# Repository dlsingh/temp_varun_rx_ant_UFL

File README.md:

this repo contains files rof varun rx with UFL antenna project

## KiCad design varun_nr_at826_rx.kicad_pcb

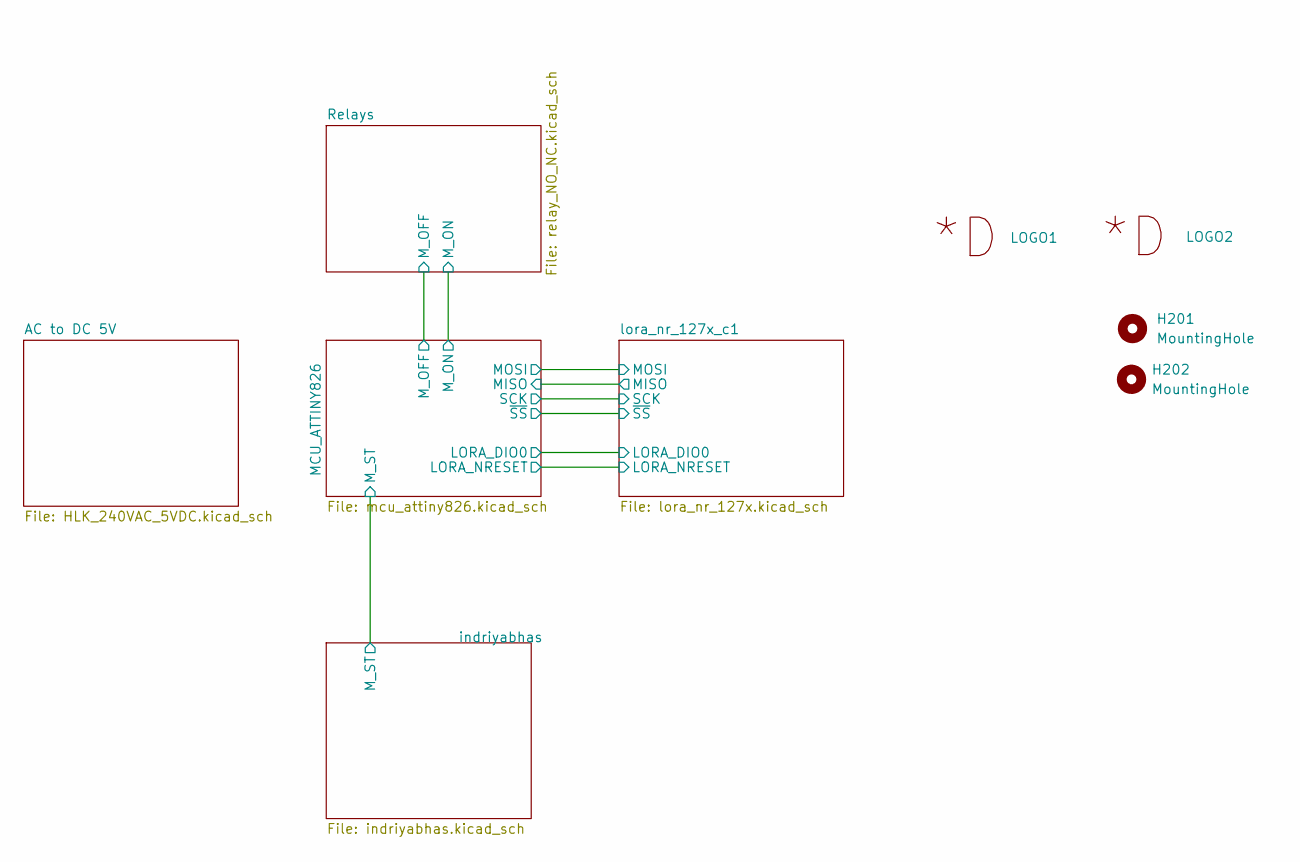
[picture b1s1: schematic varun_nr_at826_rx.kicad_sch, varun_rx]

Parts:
H201, H202: MountingHole; MountingHole_3mm
LOGO1, LOGO2: Dyulabs_logo; D_logo

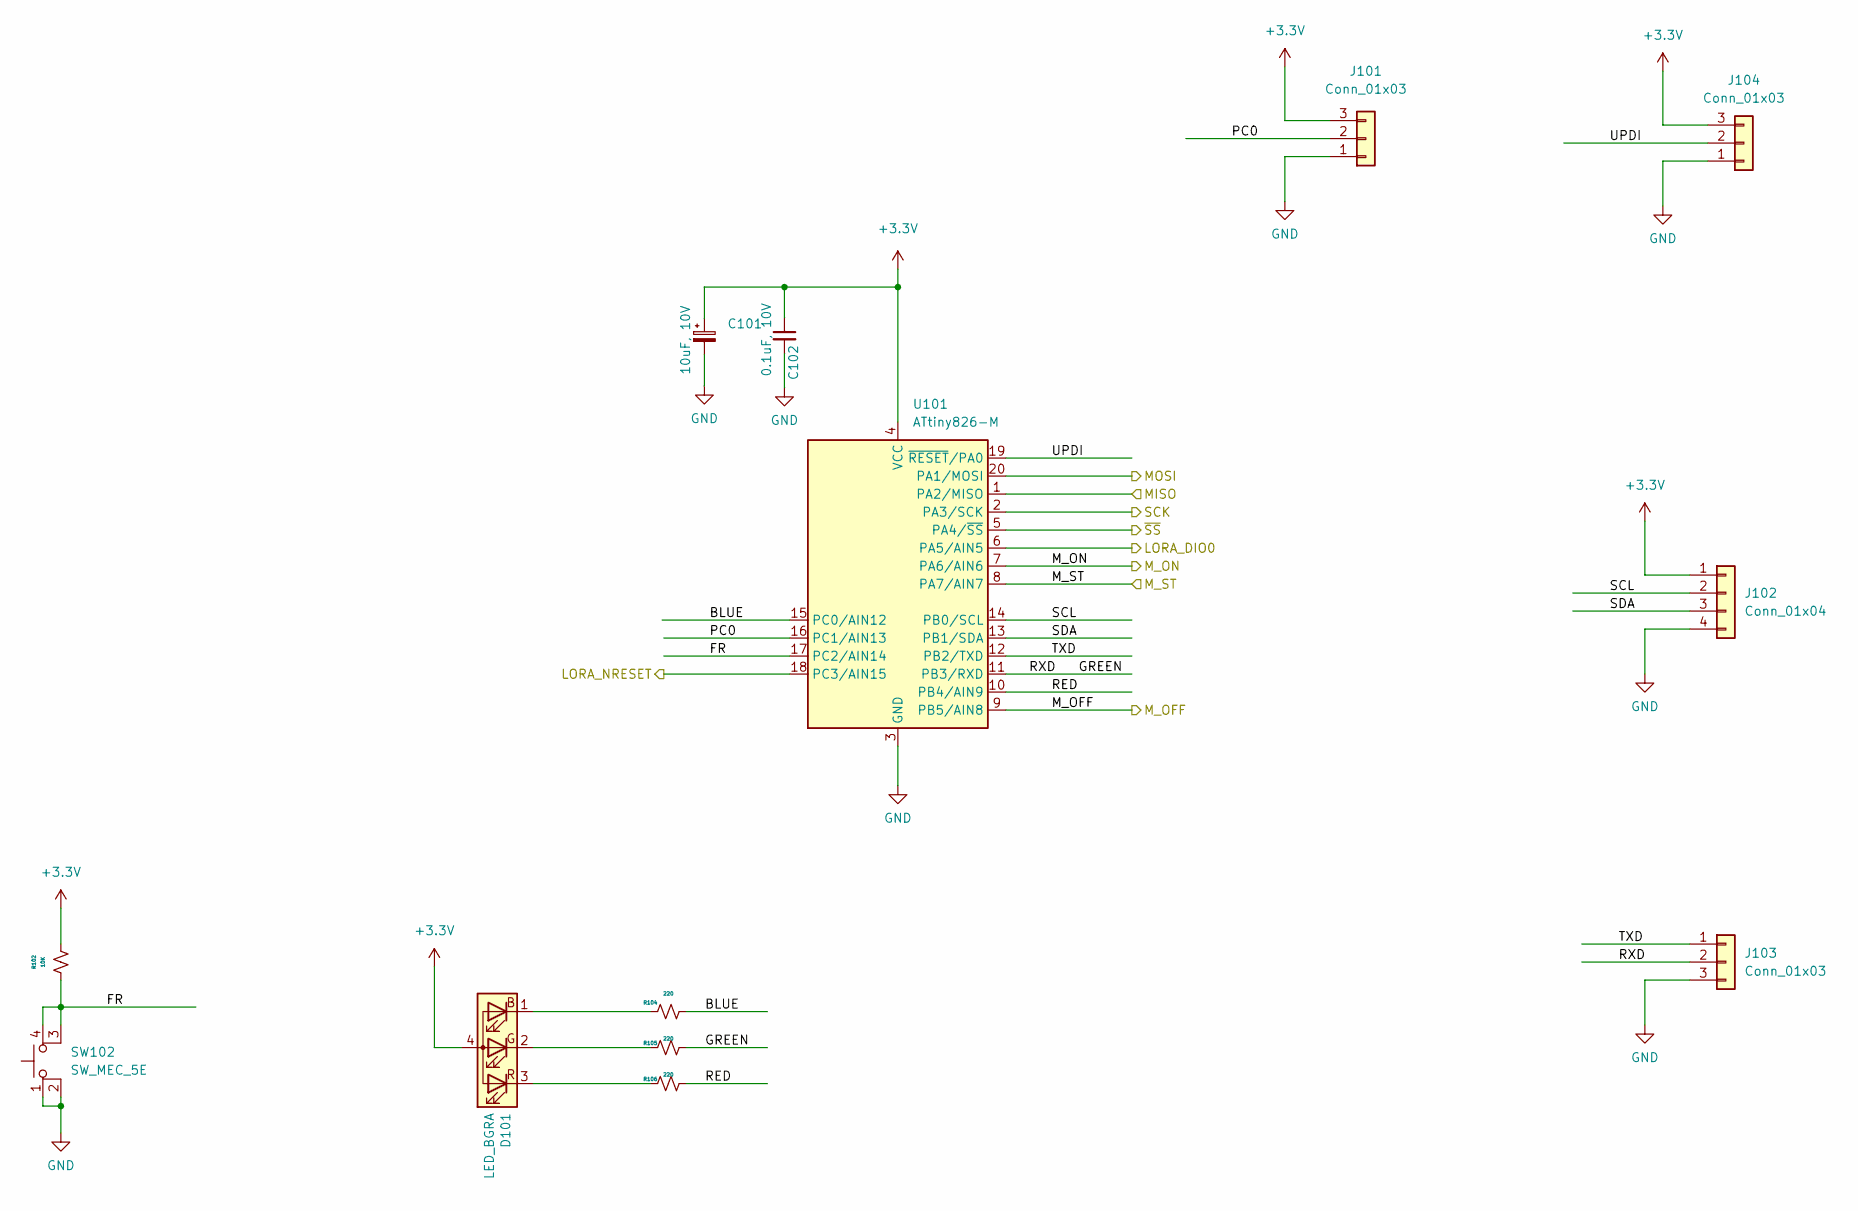
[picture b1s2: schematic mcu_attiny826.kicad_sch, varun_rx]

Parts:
C101: 10uF, 10V; C_1206_3216Metric
C102: 0.1uF, 10V; C_0402_1005Metric
D101: LED_BGRA; LED_Cree_RGB_1.00x1.00mm_P0.2mm
J101, J103: Conn_01x03; PinHeader_1x03_P2.54mm_Vertical
J102: Conn_01x04; PinHeader_1x04_P2.54mm_Vertical
J104: Conn_01x03; JST_PH_B3B-PH-K_1x03_P2.00mm_Vertical
R102: 10K; R_0402_1005Metric
R104, R105, R106: 220; R_0402_1005Metric
SW102: SW_MEC_5E; RKB2SJM250SMTR_LFS_SWITCH
U101: ATtiny826-M; VQFN-20-1EP_3x3mm_P0.4mm_EP1.7x1.7mm

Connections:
+3V3: C101.1, C102.1, D101.4 (A), J101.3, J102.1, J104.3, R102.2, U101.4 (VCC); also elsewhere on the board
/MCU_ATTINY826/BLUE: R104.1, U101.15 (PC0/AIN12)
/MCU_ATTINY826/FR: R102.1, SW102.3 (K), SW102.4 (A), U101.17 (PC2/AIN14)
/MCU_ATTINY826/GREEN: J103.2, R105.1, U101.11 (PB3/RXD)
/MCU_ATTINY826/LORA_DIO0: U101.6 (PA5/AIN5); also elsewhere on the board
/MCU_ATTINY826/LORA_NRESET: U101.18 (PC3/AIN15); also elsewhere on the board
/MCU_ATTINY826/MISO: U101.1 (PA2/MISO); also elsewhere on the board
/MCU_ATTINY826/MOSI: U101.20 (PA1/MOSI); also elsewhere on the board
/MCU_ATTINY826/M_OFF: U101.9 (PB5/AIN8); also elsewhere on the board
/MCU_ATTINY826/M_ON: U101.7 (PA6/AIN6); also elsewhere on the board
/MCU_ATTINY826/M_ST: U101.8 (PA7/AIN7); also elsewhere on the board
/MCU_ATTINY826/PC0: J101.2, U101.16 (PC1/AIN13)
/MCU_ATTINY826/RED: R106.1, U101.10 (PB4/AIN9)
/MCU_ATTINY826/SCK: U101.2 (PA3/SCK); also elsewhere on the board
/MCU_ATTINY826/SCL: J102.2, U101.14 (PB0/SCL)
/MCU_ATTINY826/SDA: J102.3, U101.13 (PB1/SDA)
/MCU_ATTINY826/TXD: J103.1, U101.12 (PB2/TXD)
/MCU_ATTINY826/UPDI: J104.2, U101.19 (~RESET/PA0)
/MCU_ATTINY826/~SS: U101.5 (PA4/~SS); also elsewhere on the board
GND: C101.2, C102.2, J101.1, J102.4, J103.3, J104.1, SW102.1, SW102.2, U101.3 (GND), U101.21 (GND); also elsewhere on the board
unnamed: D101.1 (BK), R104.2
unnamed: D101.2 (GK), R105.2
unnamed: D101.3 (RK), R106.2

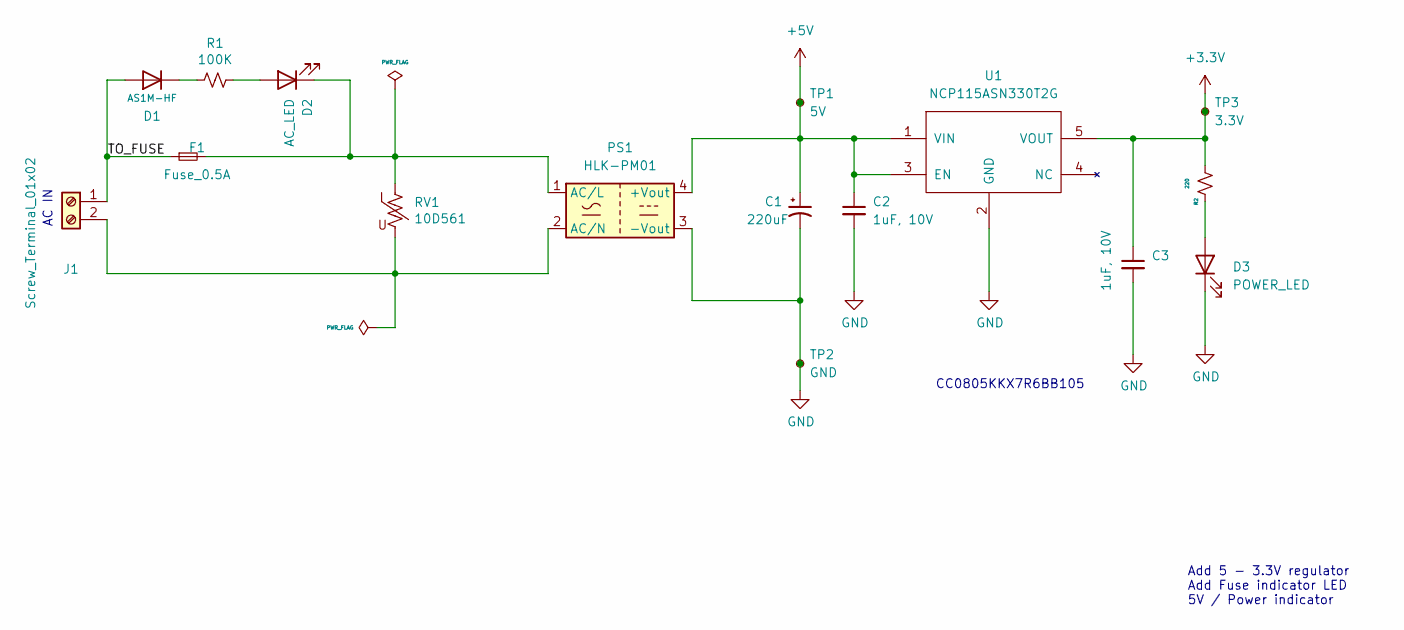
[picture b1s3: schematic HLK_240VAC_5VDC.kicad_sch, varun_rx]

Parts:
C1: 220uF; CP_Radial_D6.3mm_P2.50mm
C2, C3: 1uF, 10V; C_0805_2012Metric
D1: AS1M-HF; D_SMA
D2: AC_LED; LED_D3.0mm
D3: POWER_LED; LED_D3.0mm
F1: Fuse_0.5A; Fuse_Schurter_UMT250
J1: Screw_Terminal_01x02; CUI_TB002-500-02BE
PS1: HLK-PM01; Converter_ACDC_HiLink_HLK-PMxx
R1: 100K; R_0805_2012Metric
R2: 220; R_0402_1005Metric
RV1: 10D561; RV_Disc_D12mm_W5.1mm_P7.5mm
TP1: 5V; TestPoint_THTPad_D1.0mm_Drill0.5mm
TP2: GND; TestPoint_THTPad_D1.0mm_Drill0.5mm
TP3: 3.3V; TestPoint_THTPad_D1.0mm_Drill0.5mm
U1: NCP115ASN330T2G; TSOP-5_1.65x3.05mm_P0.95mm

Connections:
+3V3: C3.1, R2.1, TP3.1, U1.5 (VOUT); also elsewhere on the board
+5V: C1.1, C2.1, PS1.4 (+Vout), TP1.1, U1.1 (VIN), U1.3 (EN); also elsewhere on the board
/AC to DC 5V/TO_FUSE: D1.2 (A), F1.1, J1.1
GND: C1.2, C2.2, C3.2, D3.1 (K), PS1.3 (-Vout), TP2.1, U1.2 (GND); also elsewhere on the board
unnamed: D1.1 (K), R1.2
unnamed: D2.1 (K), F1.2, PS1.1 (AC/L), RV1.1
unnamed: D2.2 (A), R1.1
unnamed: D3.2 (A), R2.2
unnamed: J1.2, PS1.2 (AC/N), RV1.2

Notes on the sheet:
AC IN
CC0805KKX7R6BB105
Add 5 - 3.3V regulator Add Fuse indicator LED 5V / Power indicator

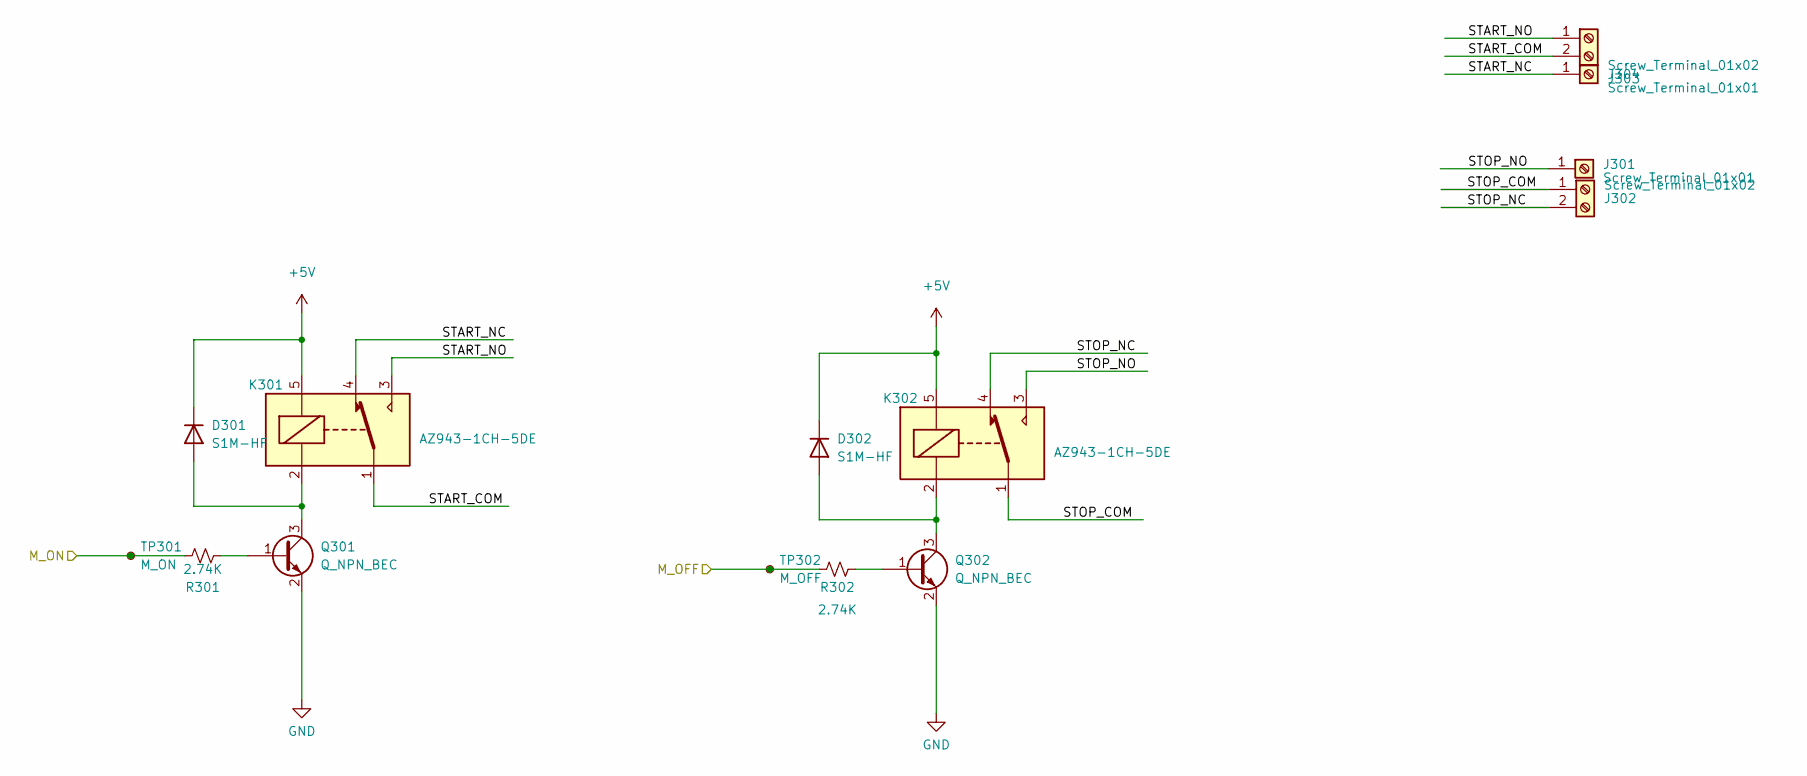
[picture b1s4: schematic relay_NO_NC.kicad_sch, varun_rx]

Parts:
D301, D302: S1M-HF; D_SMA
J301, J304: Screw_Terminal_01x01; PinHeader_1x01_P2.54mm_Vertical
J302, J303: Screw_Terminal_01x02; CUI_TB002-500-02BE
K301, K302: AZ943-1CH-5DE; Relay_SPDT_SANYOU_SRD_Series_Form_C
Q301, Q302: Q_NPN_BEC; TSOT-23
R301, R302: 2.74K; R_0402_1005Metric
TP301: M_ON; TestPoint_THTPad_D1.0mm_Drill0.5mm
TP302: M_OFF; TestPoint_THTPad_D1.0mm_Drill0.5mm

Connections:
+5V: D301.1 (K), D302.1 (K), K301.5, K302.5; also elsewhere on the board
/MCU_ATTINY826/M_OFF: R302.2, TP302.1; also elsewhere on the board
/MCU_ATTINY826/M_ON: R301.2, TP301.1; also elsewhere on the board
/Relays/START_COM: J303.2, K301.1
/Relays/START_NC: J304.1, K301.4
/Relays/START_NO: J303.1, K301.3
/Relays/STOP_COM: J302.1, K302.1
/Relays/STOP_NC: J302.2, K302.4
/Relays/STOP_NO: J301.1, K302.3
GND: Q301.2 (E), Q302.2 (E); also elsewhere on the board
unnamed: D301.2 (A), K301.2, Q301.3 (C)
unnamed: D302.2 (A), K302.2, Q302.3 (C)
unnamed: Q301.1 (B), R301.1
unnamed: Q302.1 (B), R302.1

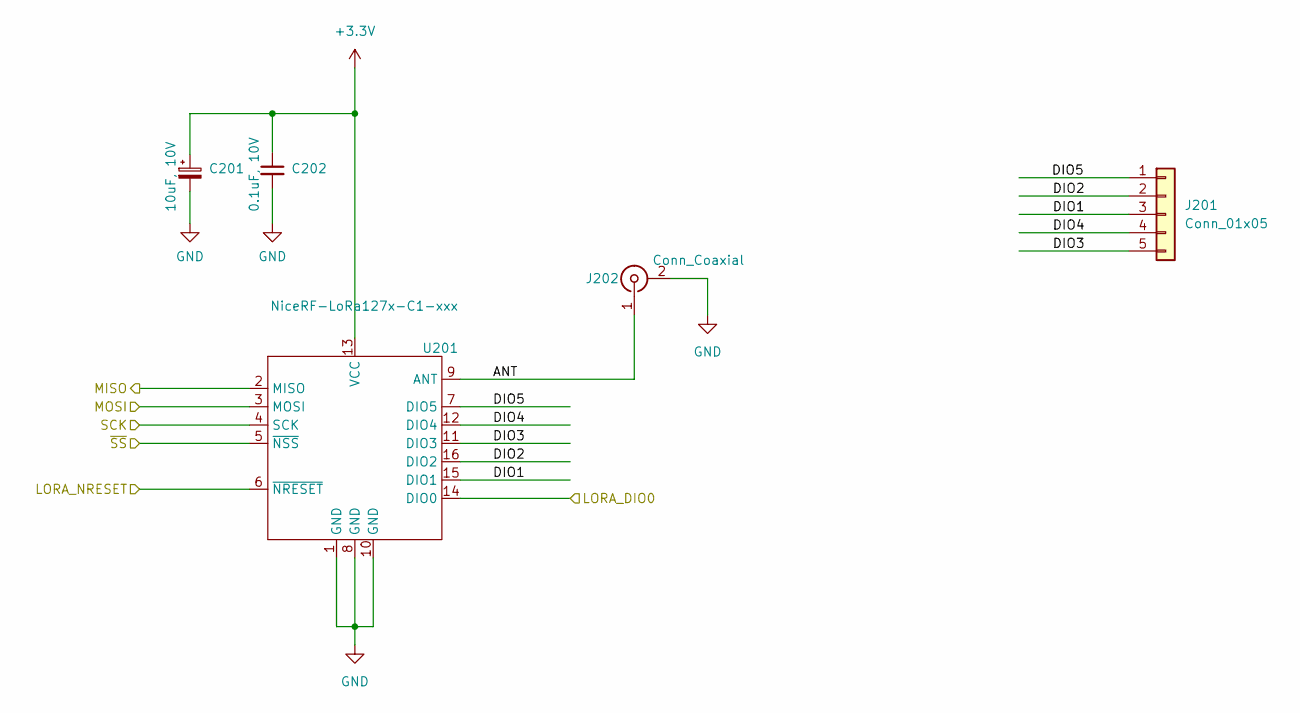
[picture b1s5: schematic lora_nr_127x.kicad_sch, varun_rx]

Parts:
C201: 10uF, 10V; C_1206_3216Metric
C202: 0.1uF, 10V; C_0402_1005Metric
J201: Conn_01x05; PinHeader_1x05_P2.54mm_Vertical
J202: Conn_Coaxial; U.FL_Molex_MCRF_73412-0110_Vertical
U201: NiceRF-LoRa127x-C1-xxx; NiceRF-LoRa127X-C1-xxx

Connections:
+3V3: C201.1, C202.1, U201.13 (VCC); also elsewhere on the board
/MCU_ATTINY826/LORA_DIO0: U201.14 (DIO0); also elsewhere on the board
/MCU_ATTINY826/LORA_NRESET: U201.6 (~NRESET); also elsewhere on the board
/MCU_ATTINY826/MISO: U201.2 (MISO); also elsewhere on the board
/MCU_ATTINY826/MOSI: U201.3 (MOSI); also elsewhere on the board
/MCU_ATTINY826/SCK: U201.4 (SCK); also elsewhere on the board
/MCU_ATTINY826/~SS: U201.5 (~NSS); also elsewhere on the board
/lora_nr_127x_c1/ANT: J202.1 (In), U201.9 (ANT)
/lora_nr_127x_c1/DIO1: J201.3, U201.15 (DIO1)
/lora_nr_127x_c1/DIO2: J201.2, U201.16 (DIO2)
/lora_nr_127x_c1/DIO3: J201.5, U201.11 (DIO3)
/lora_nr_127x_c1/DIO4: J201.4, U201.12 (DIO4)
/lora_nr_127x_c1/DIO5: J201.1, U201.7 (DIO5)
GND: C201.2, C202.2, J202.2 (Ext), U201.1 (GND), U201.8 (GND), U201.10 (GND); also elsewhere on the board

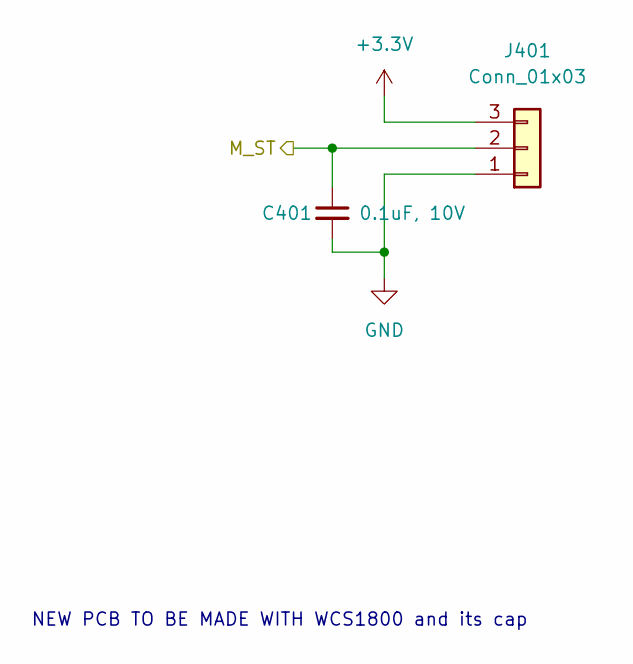
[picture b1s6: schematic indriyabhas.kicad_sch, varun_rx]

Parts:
C401: 0.1uF, 10V; C_0402_1005Metric
J401: Conn_01x03; JST_PH_B3B-PH-K_1x03_P2.00mm_Vertical

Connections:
+3V3: J401.3; also elsewhere on the board
/MCU_ATTINY826/M_ST: C401.1, J401.2; also elsewhere on the board
GND: C401.2, J401.1; also elsewhere on the board

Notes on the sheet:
NEW PCB TO BE MADE WITH WCS1800 and its cap

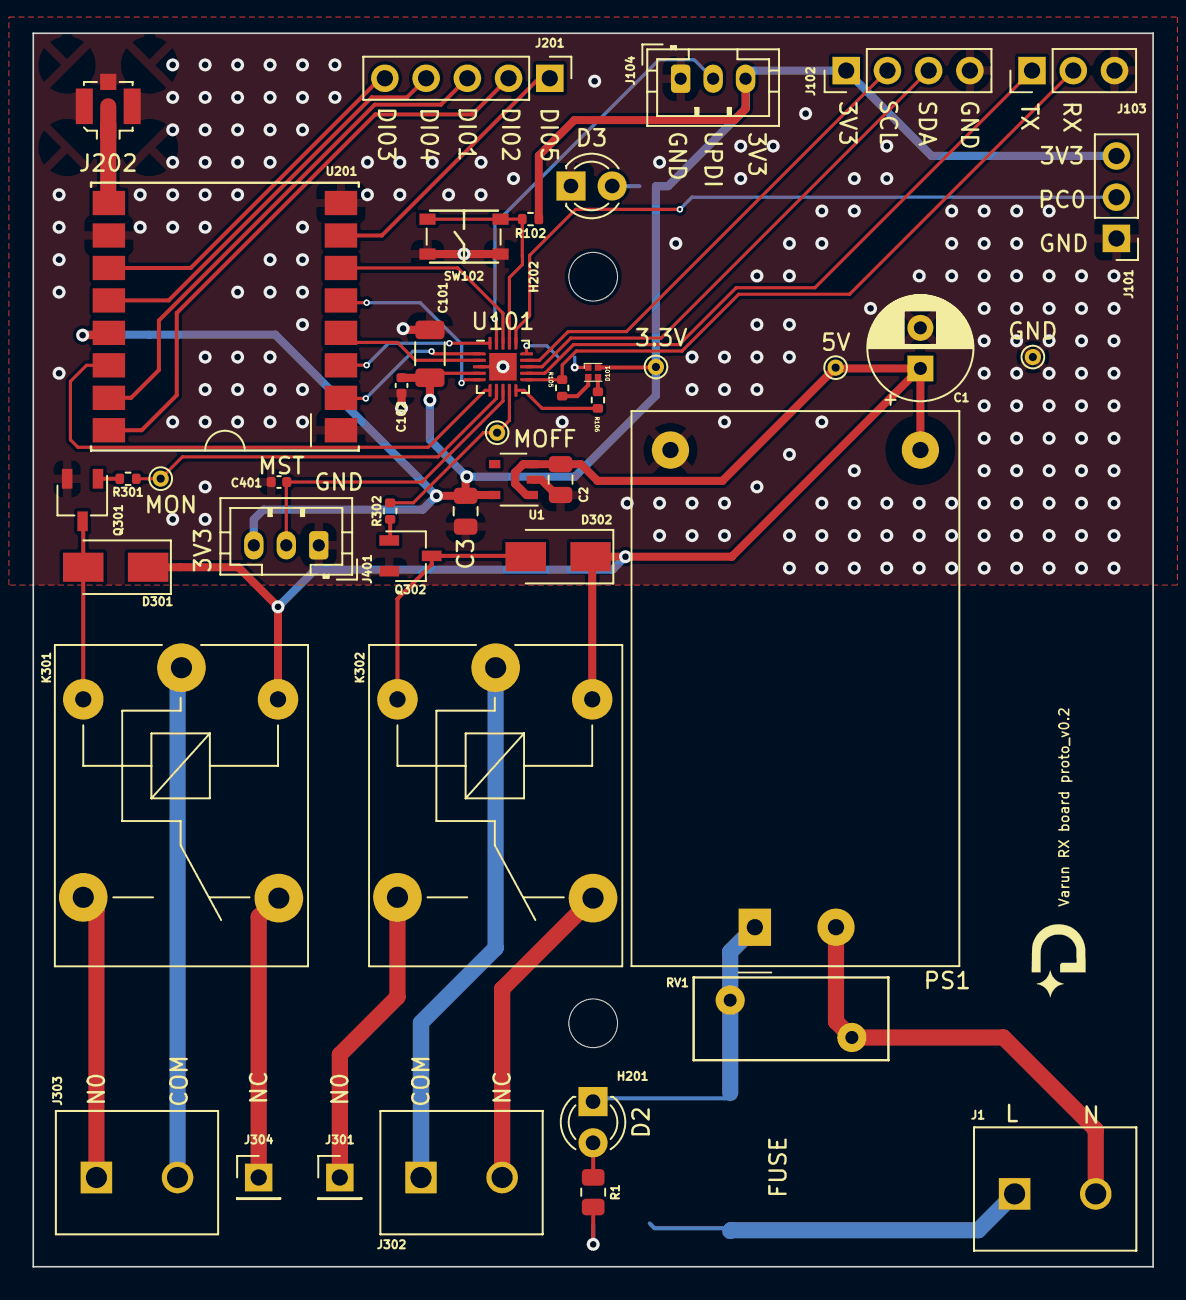
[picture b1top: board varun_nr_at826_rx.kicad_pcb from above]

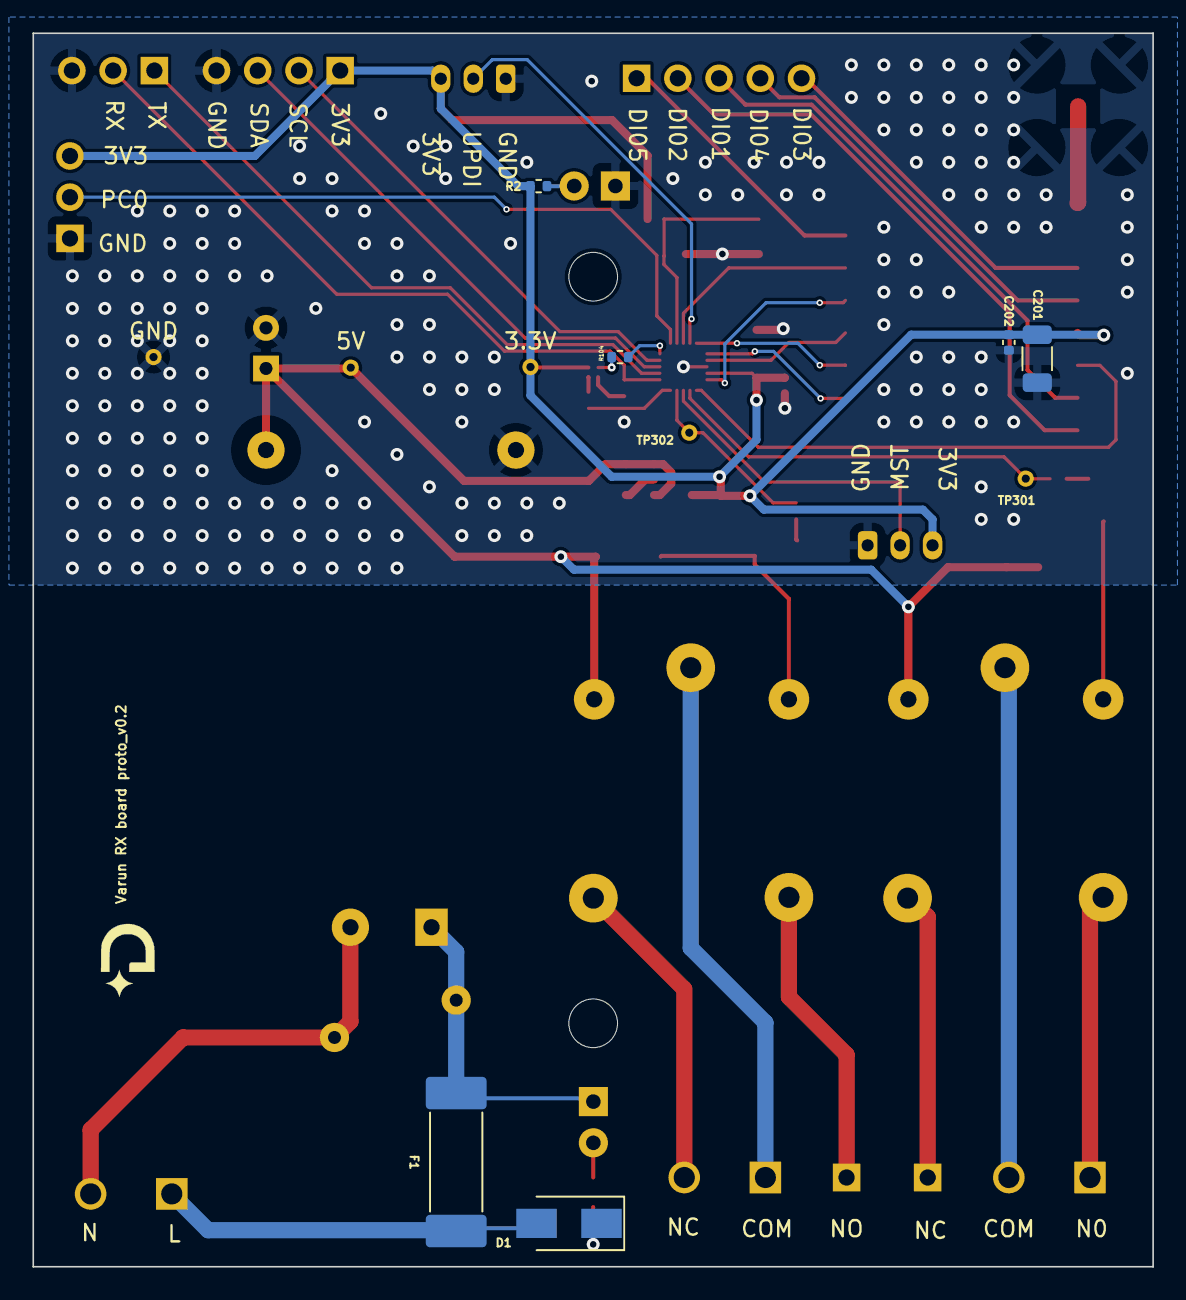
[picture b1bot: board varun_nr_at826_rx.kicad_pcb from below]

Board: 2 copper layers, 69.0 x 76.0 mm, 54 parts (7 on the bottom side), 46 nets.

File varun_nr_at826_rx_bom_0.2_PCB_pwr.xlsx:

Component | References | Value | Footprint | Supplied By | Quantity Per PCB | MFPN | Manufacturer | Distributor | Description | Vendor
1 | AE201 | SMA_Antenna |  | DYU Labs | 1 | Generic | Generic | Robu | Antenna with extra pin for shielding
2 | C1 | 220uF | CP_Radial_D6.3mm_P2.50mm | PCB Power | 1 | ESH227M010AE3AA | KEMET | Mouser | Polarized capacitor, small US symbol
3 | C102 C202 C401 | 0.1uF, 10V | C_0402_1005Metric | PCB Power | 3 | 0402ZD104KAT4A | kyocera AVX | Mouser | Unpolarized capacitor, small symbol | AVX
4 | C101 C201 | 10uF, 10V | C_1206_3216Metric | PCB Power | 2 | TAJA106K010SNJ | kyocera AVX | Mouser | Polarized capacitor, small symbol
5 | C2 C3 | 1uF, 10V | C_0805_2012Metric | PCB Power | 2 | CC0805KKX7R6BB105 | Yageo | Mouser | Unpolarized capacitor, small symbol
6 | D2 | AC_LED | LED_D3.0mm | DYU Labs | 1 | MCL034PT | Multicomp Pro | Element14 | Light emitting diode
7 | D1 | AS1M-HF | D_SMA | PCB Power | 1 | AS1M-HF | Comchip | Mouser | 1000V 1A General Purpose Rectifier Diode, DO-41
8 | D101 | LED_BGRA | LED_Cree_RGB_1.00x1.00mm_P0.2mm | PCB Power | 1 | uhd1110-fka-cl1a13r3q1bbqfmf3 | Cree LED | Mouser | RGB LED, blue/green/red/anode
9 | D3 | POWER_LED | LED_D3.0mm | DYU Labs | 1 | MCL034GT | Multicomp Pro | Element14 | Light emitting diode
10 | D301 D302 | S1M-HF | D_SMA | PCB Power | 2 | S1M-HF | Comchip | Mouser | 1000V, 1A, General Purpose Rectifier Diode, SMA(DO-214AC)
11 | F1 | Fuse_0.5A | Fuse_Schurter_UMT250 | PCB Power | 1 | 3405.0163.24 | Schurter | Mouser | Fuse, small symbol
12 | J103 | Conn_01x03 | PinHeader_1x03_P2.54mm_Vertical | DYU Labs | 1 | 22284030 | Molex | Generic | Generic connector, single row, 01x03, script generated (kicad-library-utils/sch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
13 | J104 J401 | Conn_01x03 | JST_PH_B3B-PH-K_1x03_P2.00mm_Vertical | DYU Labs | 2 | B3B-PH-KS | JST | Generic | Generic connector, single row, 01x03, script generated (kicad-library-utils/sch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
14 | J202 | Conn_Coaxial | SMA_Amphenol_901-143_Horizontal | DYU Labs | 1 | 73391-0083 | Molex | Mouser | coaxial connector (BNC, SMA, SMB, SMC, Cinch/RCA, LEMO, ...)
15 | J1 J302 J303 | Screw_Terminal_01x02 | CUI_TB002-500-02BE | PCB Power | 3 | TB002-500-02BE | CUI Devices | Mouser | Generic screw terminal, single row, 01x02, script generated (kicad-library-util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
16 | K301 K302 | AZ943-1CH-5DE | Relay_SPDT_SANYOU_SRD_Series_Form_C | PCB Power | 2 | AZ943-1CH-5DE | American Zettler | DigiKey | Omron G5LE relay, Miniature Single Pole, SPDT, 10A
17 | PS1 | HLK-PM01 | Converter_ACDC_HiLink_HLK-PMxx | DYU Labs | 1 | HLK-PM01 | HiLink | Rajguru | Compact AC/DC board mount power module 3W 5V
18 | Q301 Q302 | Q_NPN_BEC | TSOT-23 | PCB Power | 2 | PMBT3904,235 | Nexperia | Mouser | NPN transistor, base/emitter/collector
19 | R2 R104 R105 R106 | 220 | R_0402_1005Metric | PCB Power | 4 | WR04X221JTL | Walsin | Mouser | Resistor, small US symbol
20 | R301 R302 | 2.74K | R_0402_1005Metric | PCB Power | 2 | WR04X2741FTL | Walsin | Mouser | Resistor, small US symbol
21 | R102 | 10K | R_0402_1005Metric | PCB Power | 1 | WR04X103JTL | Walsin | Mouser | Resistor, small US symbol
22 | R1 | 100K | R_0805_2012Metric | PCB Power | 1 | ERJ-P06J104V | KOA Speer | Mouser | Resistor, small US symbol
23 | RV1 | 10D561 | RV_Disc_D12mm_W5.1mm_P7.5mm | PCB Power | 1 | MOV-10D561K | Bornus | Mouser | Voltage dependent resistor, US symbol
24 | SW102 | SW_MEC_5E | RKB2SJM250SMTR_LFS_SWITCH | PCB Power | 1 | PTS815 SJM 250 SMTR LFS |  | Mouser | MEC 5E single pole normally-open tactile switch
25 | U101 | ATtiny826-M | VQFN-20-1EP_3x3mm_P0.4mm_EP1.7x1.7mm | DYU Labs | 1 | ATTINY826-M | Microchip | Mouser | 20MHz, 8kB Flash, 1kB SRAM, 128B EEPROM, VQFN-20
26 | U1 | NCP115ASN330T2G | TSOP-5_1.65x3.05mm_P0.95mm | PCB Power | 1 | NCP115ASN330T2G | Onsemi | Mouser
27 | U201 | NiceRF-LoRa127x-C1-xxx | NiceRF-LoRa127X-C1-xxx | DYU Labs | 1 | Lora1276-C1-868 | NiceRF | NiceRF
Component Groups: | 30
Component Count: | 44
Fitted Components: | 41
Number of PCBs: | 1
Total components: | 41
Schematic Version: | 0.2
Schematic Date: | 44778
PCB Variant: | a
BoM Date: | 44789.477349537039
Schematic Source: | varun_nr_at826_rx.kicad_sch
KiCad Version: | Eeschema (6.0.1)

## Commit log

2022-08-17 Files of varun RX with UFL antenna added to this repo to solve git checkin issues
